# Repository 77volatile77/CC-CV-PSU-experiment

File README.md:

Either clone the project or use KiCanvas to quickly view the schematic and layout.

# TODO
- [x] finish stitching vias
- [x] tent vias
- [x] make sure everything is good with DRC after the above changes are done

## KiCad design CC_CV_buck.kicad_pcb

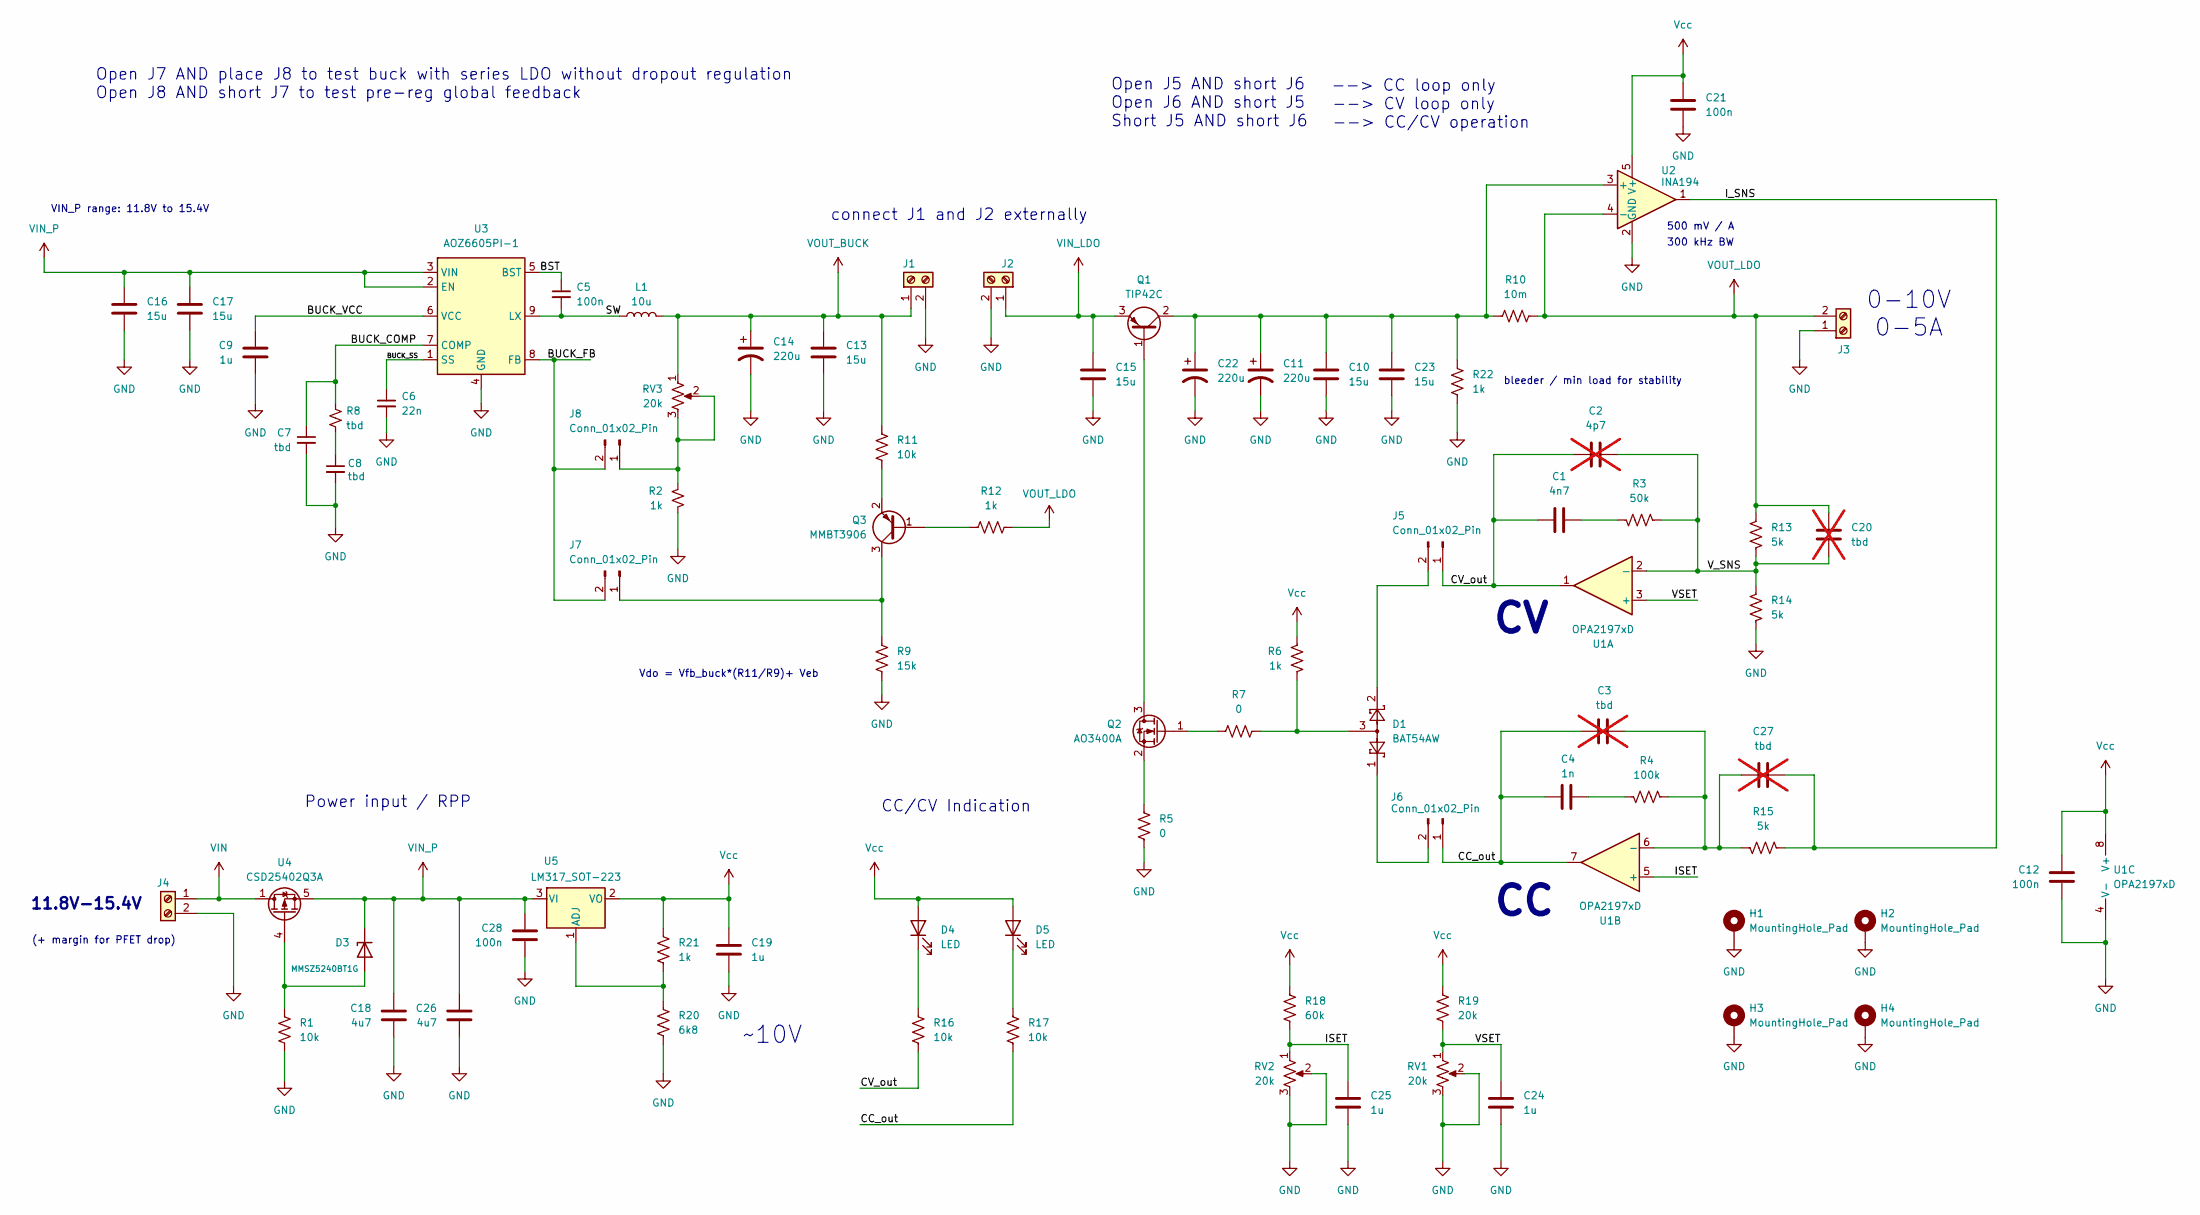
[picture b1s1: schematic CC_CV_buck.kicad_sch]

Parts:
C1: 4n7; C_0805_2012Metric_Pad1.18x1.45mm_HandSolder
C2: 4p7; C_0805_2012Metric_Pad1.18x1.45mm_HandSolder; not fitted
C3, C20, C27: tbd; C_0805_2012Metric_Pad1.18x1.45mm_HandSolder; not fitted
C4: 1n; C_0805_2012Metric_Pad1.18x1.45mm_HandSolder
C5, C12, C21, C28: 100n; C_0805_2012Metric_Pad1.18x1.45mm_HandSolder
C6: 22n; C_0805_2012Metric_Pad1.18x1.45mm_HandSolder
C7, C8: tbd; C_0805_2012Metric_Pad1.18x1.45mm_HandSolder
C9, C19, C24, C25: 1u; C_0805_2012Metric_Pad1.18x1.45mm_HandSolder
C10, C13, C15, C16, C17, C23: 15u; C_1210_3225Metric_Pad1.33x2.70mm_HandSolder
C11, C14, C22: 220u; CP_Radial_D8.0mm_P3.50mm
C18, C26: 4u7; C_0805_2012Metric_Pad1.18x1.45mm_HandSolder
D1: BAT54AW; SOT-323_SC-70
D3: MMSZ5240BT1G; D_SOD-123
D4, D5: LED; LED_0603_1608Metric
H1, H2, H3, H4: MountingHole_Pad; MountingHole_2.2mm_M2_ISO7380_Pad
J1, J2, J3, J4: TerminalBlock_Phoenix_MPT-0,5-2-2.54_1x02_P2.54mm_Horizontal
J5, J6, J7, J8: Conn_01x02_Pin; PinHeader_1x02_P1.27mm_Vertical
L1: 10u; L_Abracon_ASPI-1040HI
Q1: TIP42C; TO-220-3_Vertical
Q2: AO3400A; SOT-23
Q3: MMBT3906; SOT-23
R1, R11, R16, R17: 10k; R_0805_2012Metric_Pad1.20x1.40mm_HandSolder
R2, R6, R12, R21, R22: 1k; R_0805_2012Metric_Pad1.20x1.40mm_HandSolder
R3: 50k; R_0805_2012Metric_Pad1.20x1.40mm_HandSolder
R4: 100k; R_0805_2012Metric_Pad1.20x1.40mm_HandSolder
R5, R7: 0; R_0805_2012Metric_Pad1.20x1.40mm_HandSolder
R8: tbd; R_0805_2012Metric_Pad1.20x1.40mm_HandSolder
R9: 15k; R_0805_2012Metric_Pad1.20x1.40mm_HandSolder
R10: 10m; R_0805_2012Metric_Pad1.20x1.40mm_HandSolder
R13, R14, R15: 5k; R_0805_2012Metric_Pad1.20x1.40mm_HandSolder
R18: 60k; R_0805_2012Metric_Pad1.20x1.40mm_HandSolder
R19: 20k; R_0805_2012Metric_Pad1.20x1.40mm_HandSolder
R20: 6k8; R_0805_2012Metric_Pad1.20x1.40mm_HandSolder
RV1, RV2, RV3: 20k; POT_PTN16-A20120K1B1
U1: OPA2197xD; SOIC-8_3.9x4.9mm_P1.27mm
U2: INA194; SOT-23-5
U3: AOZ6605PI-1; SO8_EP1_AOS-L
U4: CSD25402Q3A; VSON-8_3.3x3.3mm_P0.65mm_NexFET
U5: LM317_SOT-223; SOT-223-3_TabPin2

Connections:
/BST: C5.1, U3.5 (BST)
/BUCK_COMP: C7.1, R8.1, U3.7 (COMP)
/BUCK_FB: J7.2, J8.2, U3.8 (FB)
/BUCK_SS: C6.1, U3.1 (SS)
/BUCK_VCC: C9.1, U3.6 (VCC)
/CC_out: C3.2, C4.2, J6.1, R17.2, U1.7
/CV_out: C1.2, C2.2, J5.1, R16.2, U1.1
/ISET: C25.1, R18.2, RV2.1, U1.5 (+)
/I_SNS: C27.2, R15.1, U2.1
/SW: C5.2, L1.1, U3.9 (LX)
/VSET: C24.1, R19.2, RV1.1, U1.3 (+)
/V_SNS: C2.1, C20.2, R3.1, R13.2, R14.1, U1.2 (-)
GND: C6.2, C7.2, C8.2, C9.2, C10.2, C11.2, C12.2, C13.2, C14.2, C15.2, C16.2, C17.2, C18.2, C19.2, C21.2, C22.2, C23.2, C24.2, C25.2, C26.2, C28.2, H1.1, H2.1, H3.1, H4.1, J1.2, J2.2, J3.1, J4.2, R1.2, R2.2, R5.1, R9.2, R14.2, R20.2, R22.1, RV1.2, RV1.3, RV2.2, RV2.3, U1.4 (V-), U2.2 (GND), U3.4 (GND)
unnamed: C1.1, R3.2
unnamed: C4.1, R4.2
unnamed: C8.1, R8.2
unnamed: D1.3, R6.1, R7.1
unnamed: D3.2 (A), R1.1, U4.4 (G)
unnamed: D4.1 (K), R16.1
unnamed: D5.1 (K), R17.1
unnamed: D1.2, J5.2
unnamed: D1.1, J6.2
unnamed: J7.1, Q3.3 (C), R9.1
unnamed: J8.1, R2.1, RV3.2, RV3.3
unnamed: Q1.1 (B), Q2.3 (D)
unnamed: C10.1, C11.1, C22.1, C23.1, Q1.2 (C), R10.1, R22.2, U2.3 (+)
unnamed: Q2.1 (G), R7.2
unnamed: Q2.2 (S), R5.2
unnamed: Q3.1 (B), R12.1
unnamed: Q3.2 (E), R11.2
unnamed: C3.1, C27.1, R4.1, R15.2, U1.6 (-)
unnamed: R20.1, R21.2, U5.1 (ADJ)
VIN: J4.1, U4.1 (D), U4.2 (D), U4.3 (D)
VIN_LDO: C15.1, J2.1, Q1.3 (E)
VIN_P: C16.1, C17.1, C18.1, C26.1, C28.1, D3.1 (K), U3.2 (EN), U3.3 (VIN), U4.5 (S), U5.3 (VI)
VOUT_BUCK: C13.1, C14.1, J1.1, L1.2, R11.1, RV3.1
VOUT_LDO: C20.1, J3.2, R10.2, R12.2, R13.1, U2.4 (-)
Vcc: C12.1, C19.1, C21.1, D4.2 (A), D5.2 (A), R6.2, R18.1, R19.1, R21.1, U1.8 (V+), U2.5 (V+), U5.2 (VO)

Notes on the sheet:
Open J7 AND place J8 to test buck with series LDO without dropout regulation Open J8 AND short J7 to test pre-reg global feedback
Vdo = Vfb_buck*(R11/R9)+ Veb
~10V
0-10V 0-5A
Open J5 AND short J6 Open J6 AND short J5 Short J5 AND short J6
bleeder / min load for stability
500 mV / A
(+ margin for PFET drop)
VIN_P range: 11.8V to 15.4V
300 kHz BW
11.8V-15.4V
connect J1 and J2 externally
--> CC loop only --> CV loop only --> CC/CV operation
CC/CV Indication
Power input / RPP

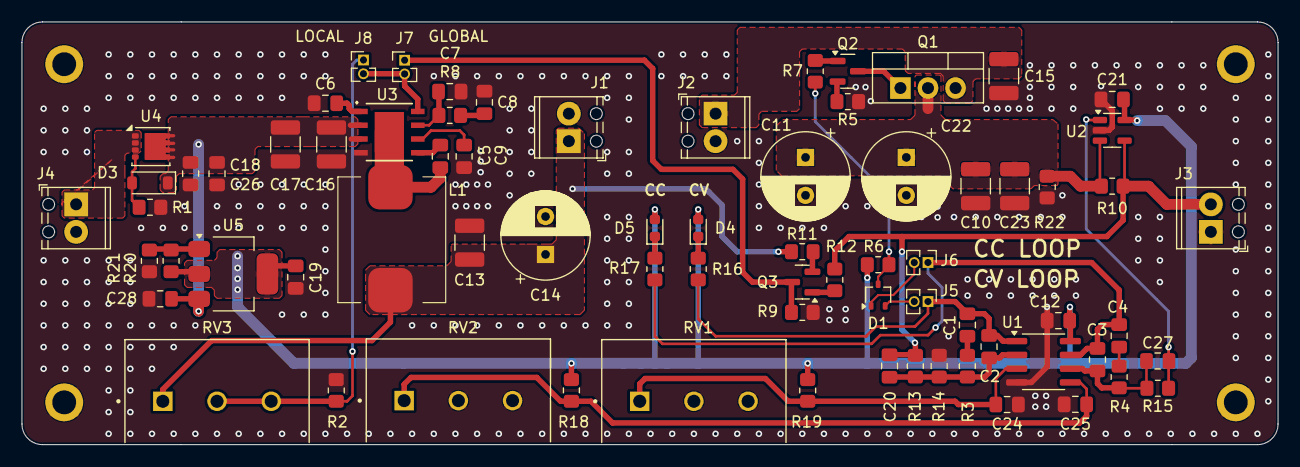
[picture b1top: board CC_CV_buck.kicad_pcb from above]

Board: 4 copper layers, 115.9 x 39.0 mm, 78 parts (0 on the bottom side), 38 nets.

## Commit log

2026-03-16 add pcb
2026-03-16 configure gitignore
2026-03-16 did a bunch of stuff
2026-03-16 added block terminals
2026-03-19 buncha stuff
2026-03-21 uhh like alot of stuff
2026-03-21 pcb stuff
2026-03-21 clean pcb a little
2026-03-22 sorta finalize component placement as well as schematic
2026-03-27 add readme
2026-03-27 add comp values for LDO, mess with layout a bit to see MH placement
2026-03-28 more or less done w/ schematic and component placement
2026-03-30 do a bunch of polygon pours
2026-03-31 editing some polygons
2026-04-05 change regulator and finish layout
2026-04-05 clean silkscreen and refdes
2026-04-05 change R7 to 0 ohm instead of 1 ohm
2026-04-05 add series resistor to potentiometers to limit maximum setpoint voltages
2026-04-06 add some stitching
2026-04-06 edit readme
2026-04-06 quick DRC
2026-04-10 for some reason RV1-2 series resistors vanished from schematic, fixed
2026-04-19 finish stiching and DRC check
2026-04-19 update todo list
